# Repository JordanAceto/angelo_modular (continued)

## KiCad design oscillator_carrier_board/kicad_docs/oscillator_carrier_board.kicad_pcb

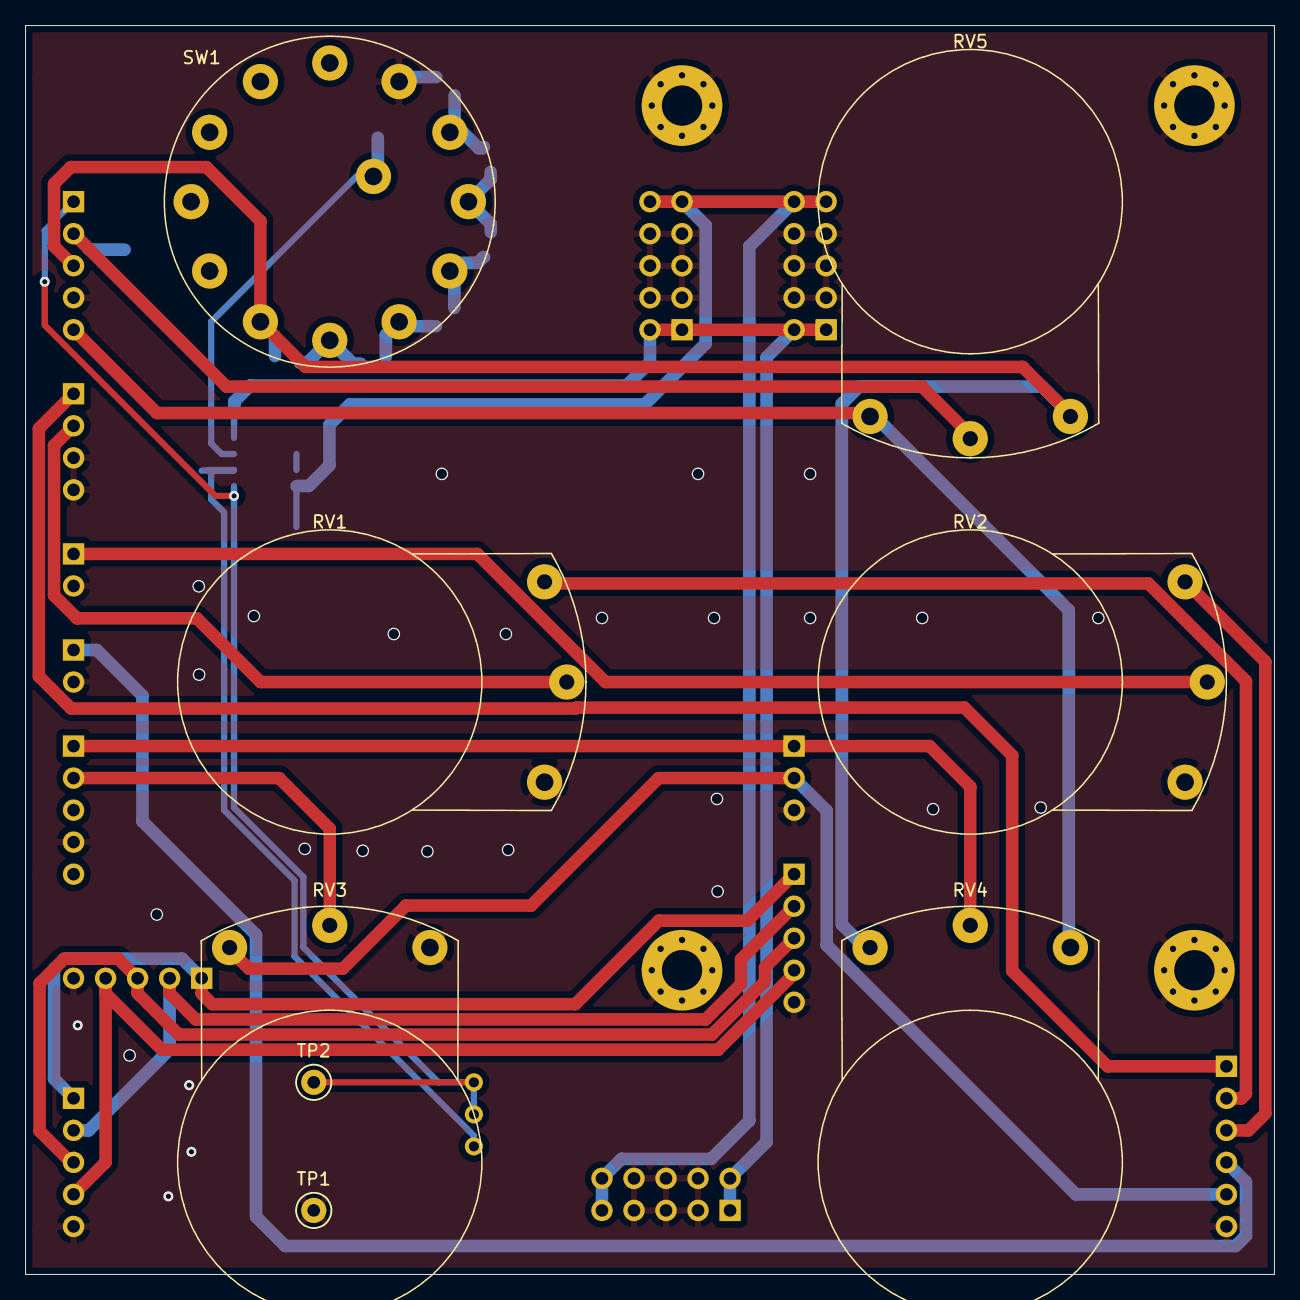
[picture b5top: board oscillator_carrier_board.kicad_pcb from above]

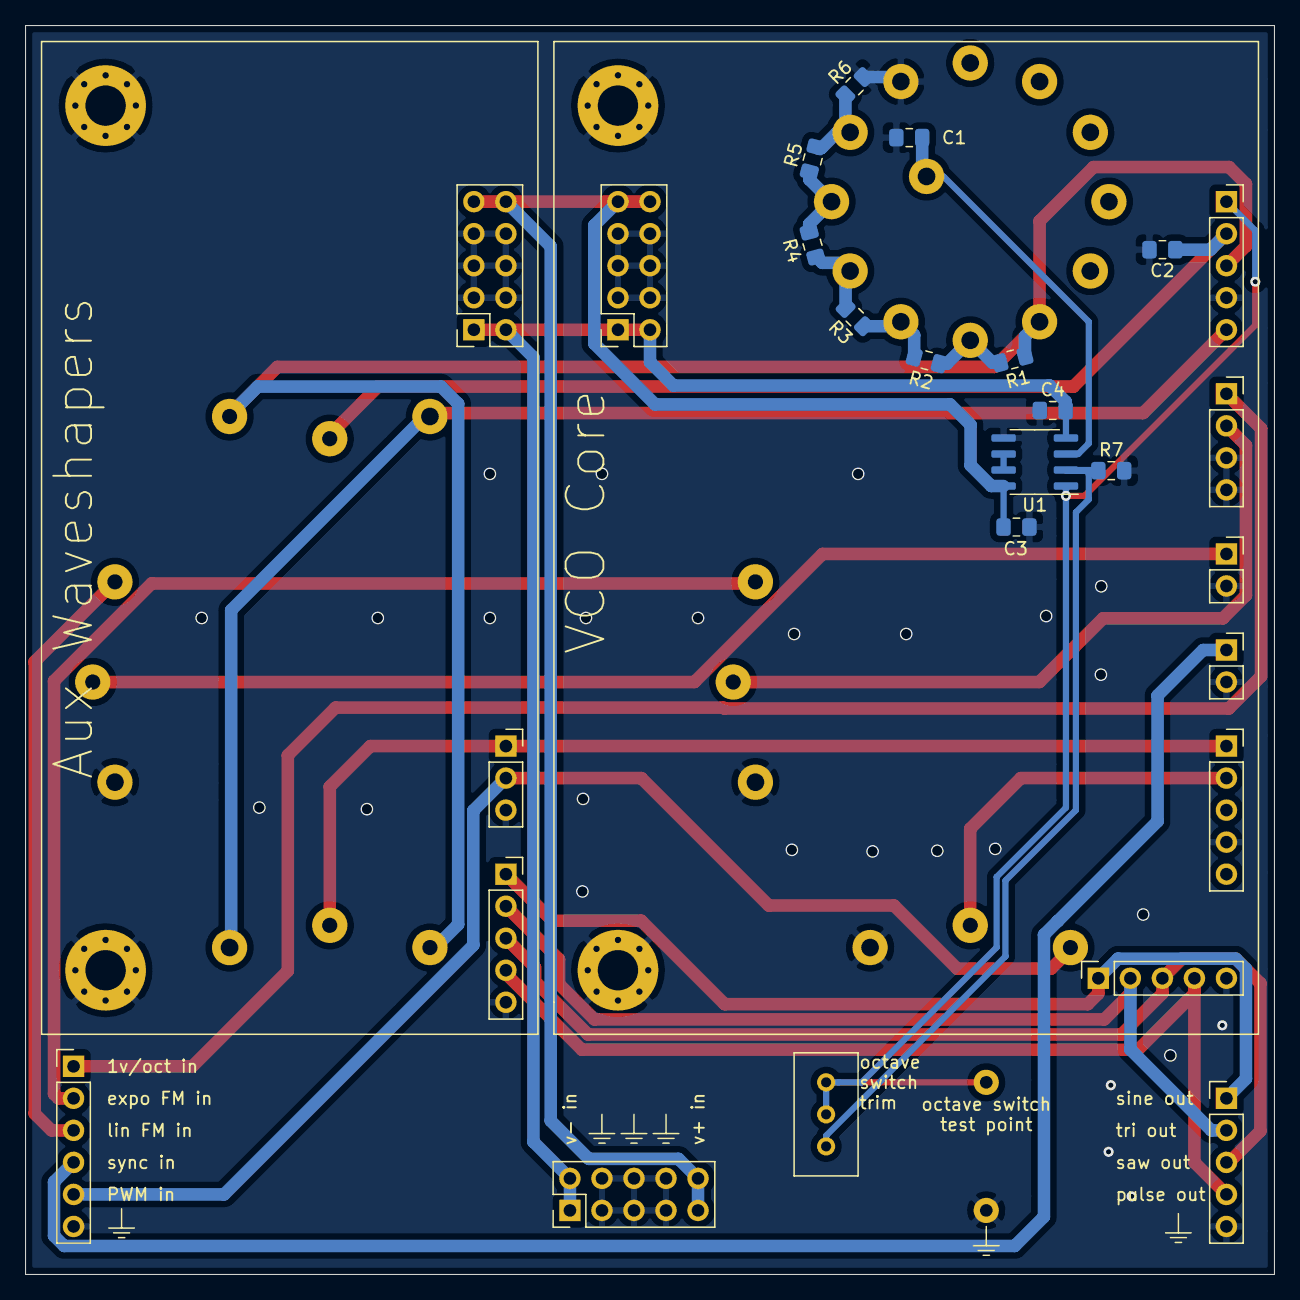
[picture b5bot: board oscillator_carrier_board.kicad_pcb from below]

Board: 2 copper layers, 99.1 x 99.1 mm, 38 parts (26 on the bottom side), 28 nets.

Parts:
C1, C2, C3, C4: 100nF; C_0805_2012Metric_Pad1.15x1.40mm_HandSolder
H1, H2, H3, H4: MountingHole_Pad; MountingHole_3.2mm_M3_Pad_Via
J1: Conn_01x06; PinHeader_1x06_P2.54mm_Vertical
J2: Conn_01x05; PinHeader_1x05_P2.54mm_Vertical
J3: power_header; PinHeader_2x05_P2.54mm_Vertical
J4: Conn_01x04; PinSocket_1x04_P2.54mm_Vertical
J5, J6: Conn_01x02; PinSocket_1x02_P2.54mm_Vertical
J7, J10, J11: Conn_01x05; PinSocket_1x05_P2.54mm_Vertical
J8, J13: power_header; PinSocket_2x05_P2.54mm_Vertical
J9: to_VCO_board; PinSocket_1x05_P2.54mm_Vertical
J12: Conn_01x03; PinSocket_1x03_P2.54mm_Vertical
R1, R2, R3, R4, R5, R6: 10k; R_0805_2012Metric_Pad1.15x1.40mm_HandSolder
R7: ???; R_0805_2012Metric_Pad1.15x1.40mm_HandSolder
RV1, RV2, RV3, RV4, RV5: 100k; alpha_RV24AF-40
RV6: ???; Potentiometer_Bourns_3296W_Vertical
SW1: octave_switch; apha_SR2612F-0112
TP1, TP2: TestPoint; TestPoint_Keystone_5000-5004_Miniature
U1: TL072; SOIC-8_3.9x4.9mm_P1.27mm

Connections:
+5V: J7.3, J10.3, R1.2, RV4.3, RV5.3, SW1.7
+12V: C3.1, J3.9, J3.10, J8.9, J8.10, J13.9, J13.10, U1.8
-5V: J7.5, J10.5, RV4.1, RV5.1
-12V: C4.2, J3.1, J3.2, J8.1, J8.2, J13.1, J13.2, U1.4
/VCO_core_components/1v_oct_in: J1.1, J4.1
/VCO_core_components/PWM_in: J1.5, J12.2, RV3.3
/VCO_core_components/expo_FM_in: J1.2, RV1.3
/VCO_core_components/lin_FM_in: J1.3, RV2.3
/VCO_core_components/sync_in: J1.4, J6.1
/aux_waveshaper_components/man_pulse_in: J7.1, J12.1, RV4.2
/aux_waveshaper_components/pulse_in: J2.4, J9.4, J11.4
/aux_waveshaper_components/saw_in: J2.3, J9.3, J11.3
/aux_waveshaper_components/sine_in: J2.1, J9.1, J11.1
/aux_waveshaper_components/tri_in: J2.2, J9.2, J11.2
GND: C1.2, C2.2, C3.2, C4.1, H1.1, H2.1, H3.1, H4.1, J1.6, J2.5, J3.3, J3.4, J3.5, J3.6, J3.7, J3.8, J4.3, J4.4, J5.2, J6.2, J7.4, J8.3, J8.4, J8.5, J8.6, J8.7, J8.8, J9.5, J10.4, J11.5, J12.3, J13.3, J13.4, J13.5, J13.6, J13.7, J13.8, R6.1, R7.2, RV1.1, RV2.1, RV3.1, SW1.1, TP1.1, U1.5
unnamed: C1.1, SW1.13, U1.3
unnamed: C2.1, J10.2, RV5.2
unnamed: J4.2, RV1.2
unnamed: J5.1, RV2.2
unnamed: J7.2, RV3.2
unnamed: J10.1, RV6.2, RV6.3, TP2.1, U1.1
unnamed: R1.1, R2.2, SW1.6
unnamed: R2.1, R3.2, SW1.5
unnamed: R3.1, R4.2, SW1.4
unnamed: R4.1, R5.2, SW1.3
unnamed: R5.1, R6.2, SW1.2
unnamed: R7.1, RV6.1, U1.2
unnamed: U1.6, U1.7

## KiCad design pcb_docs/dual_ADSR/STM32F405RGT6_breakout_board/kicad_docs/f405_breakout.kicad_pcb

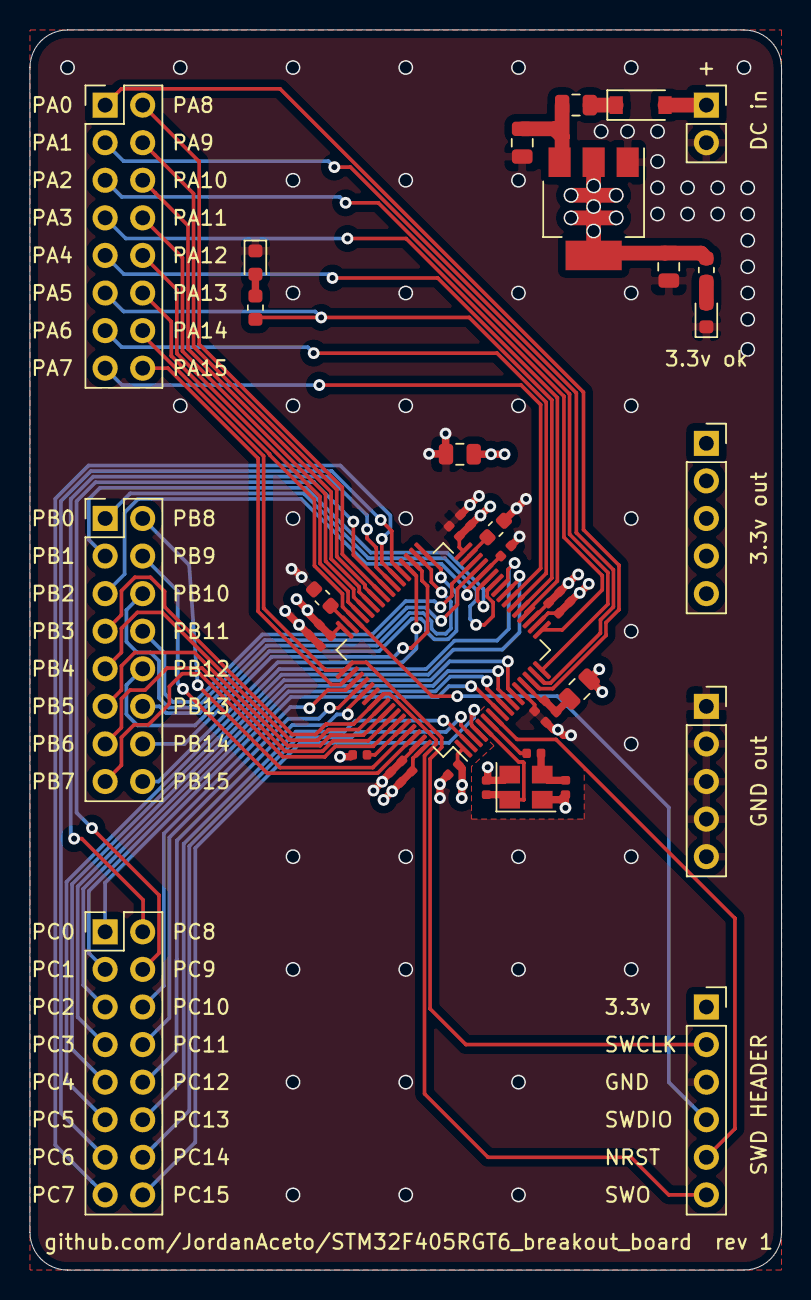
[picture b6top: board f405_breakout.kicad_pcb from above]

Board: 4 copper layers, 50.8 x 83.8 mm, 38 parts (0 on the bottom side), 63 nets.

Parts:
C1, C4, C8: 10uF; C_0805_2012Metric
C2, C3, C6, C7, C9, C10, C11, C12, C13, C14: 100nF; C_0402_1005Metric
C5: 10nF; C_0402_1005Metric
C15, C16: 2.2uF; C_0603_1608Metric
C17, C18: 12pF; C_0402_1005Metric
D1: B5819W; D_SOD-123
D2: power_LED; LED_0603_1608Metric
D3: user_LED; LED_0603_1608Metric
FB1, FB2: 100R @ 100MHz; L_0805_2012Metric
HSE1: 16MHz; Crystal_SMD_3225-4Pin_3.2x2.5mm
J1: DC_in; PinSocket_1x02_P2.54mm_Vertical
J2: SWD; PinSocket_1x06_P2.54mm_Vertical
J3: 3.3v_out; PinSocket_1x05_P2.54mm_Vertical
J4: gnd_out; PinSocket_1x05_P2.54mm_Vertical
J5: port_A; PinHeader_2x08_P2.54mm_Vertical
J6: port_B; PinHeader_2x08_P2.54mm_Vertical
J7: port_C; PinHeader_2x08_P2.54mm_Vertical
R1, R3: 2k2; R_0603_1608Metric
R2, R4: 10k; R_0402_1005Metric
R5: 100; R_0402_1005Metric
U1: AMS1117-3.3; SOT-223-3_TabPin2
U2: STM32F405RGT6; LQFP-64_10x10mm_P0.5mm

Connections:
+3.3VA: C2.1, C5.1, FB1.1, U2.13
+3V3: C1.1, C3.1, C6.1, C7.1, C8.1, C9.1, C10.1, C11.1, C12.1, C13.1, C14.1, FB1.2, J2.1, J3.1, J3.2, J3.3, J3.4, J3.5, R1.2, U1.2, U2.1, U2.19, U2.32, U2.48, U2.64
BOOT0: R2.2, U2.60
GND: C1.2, C2.2, C3.2, C4.2, C5.2, C6.2, C7.2, C8.2, C9.2, C10.2, C11.2, C12.2, C13.2, C14.2, C15.2, C16.2, C17.2, C18.2, D2.1, D3.1, HSE1.2, HSE1.4, J1.2, J2.3, J4.1, J4.2, J4.3, J4.4, J4.5, R2.1, R4.1, U1.1, U2.12, U2.18, U2.63
NRST: J2.5, U2.7
unnamed: C4.1, FB2.1, U1.3
unnamed: C15.1, U2.31
unnamed: C16.1, U2.47
unnamed: C18.1, HSE1.3, R5.2
unnamed: D1.1, FB2.2
unnamed: D2.2, R1.1
unnamed: D3.2, R3.1
PA0: J5.1, U2.14
PA1: J5.3, U2.15
PA2: J5.5, U2.16
PA3: J5.7, U2.17
PA4: J5.9, U2.20
PA5: J5.11, R3.2, U2.21
PA6: J5.13, U2.22
PA7: J5.15, U2.23
PA8: J5.2, U2.41
PA9: J5.4, U2.42
PA10: J5.6, U2.43
PA11: J5.8, U2.44
PA12: J5.10, U2.45
PA13_SWDIO: J2.4, J5.12, U2.46
PA14_SWCLK: J2.2, J5.14, U2.49
PA15: J5.16, U2.50
PB0: J6.1, U2.26
PB1: J6.3, U2.27
PB2_BOOT1: J6.5, R4.2, U2.28
PB3_SWO: J2.6, J6.7, U2.55
PB4: J6.9, U2.56
PB5: J6.11, U2.57
PB6: J6.13, U2.58
PB7: J6.15, U2.59
PB8: J6.2, U2.61
PB9: J6.4, U2.62
PB10: J6.6, U2.29
PB11: J6.8, U2.30
PB12: J6.10, U2.33
PB13: J6.12, U2.34
PB14: J6.14, U2.35
PB15: J6.16, U2.36
PC0: J7.1, U2.8
PC1: J7.3, U2.9
PC2: J7.5, U2.10
PC3: J7.7, U2.11
PC4: J7.9, U2.24
PC5: J7.11, U2.25
PC6: J7.13, U2.37
PC7: J7.15, U2.38
PC8: J7.2, U2.39
PC9: J7.4, U2.40
PC10: J7.6, U2.51
PC11: J7.8, U2.52
PC12: J7.10, U2.53
PC13: J7.12, U2.2
PC14: J7.14, U2.3
PC15: J7.16, U2.4
PH0: C17.1, HSE1.1, U2.5
PH1: R5.1, U2.6
VCC: D1.2, J1.1

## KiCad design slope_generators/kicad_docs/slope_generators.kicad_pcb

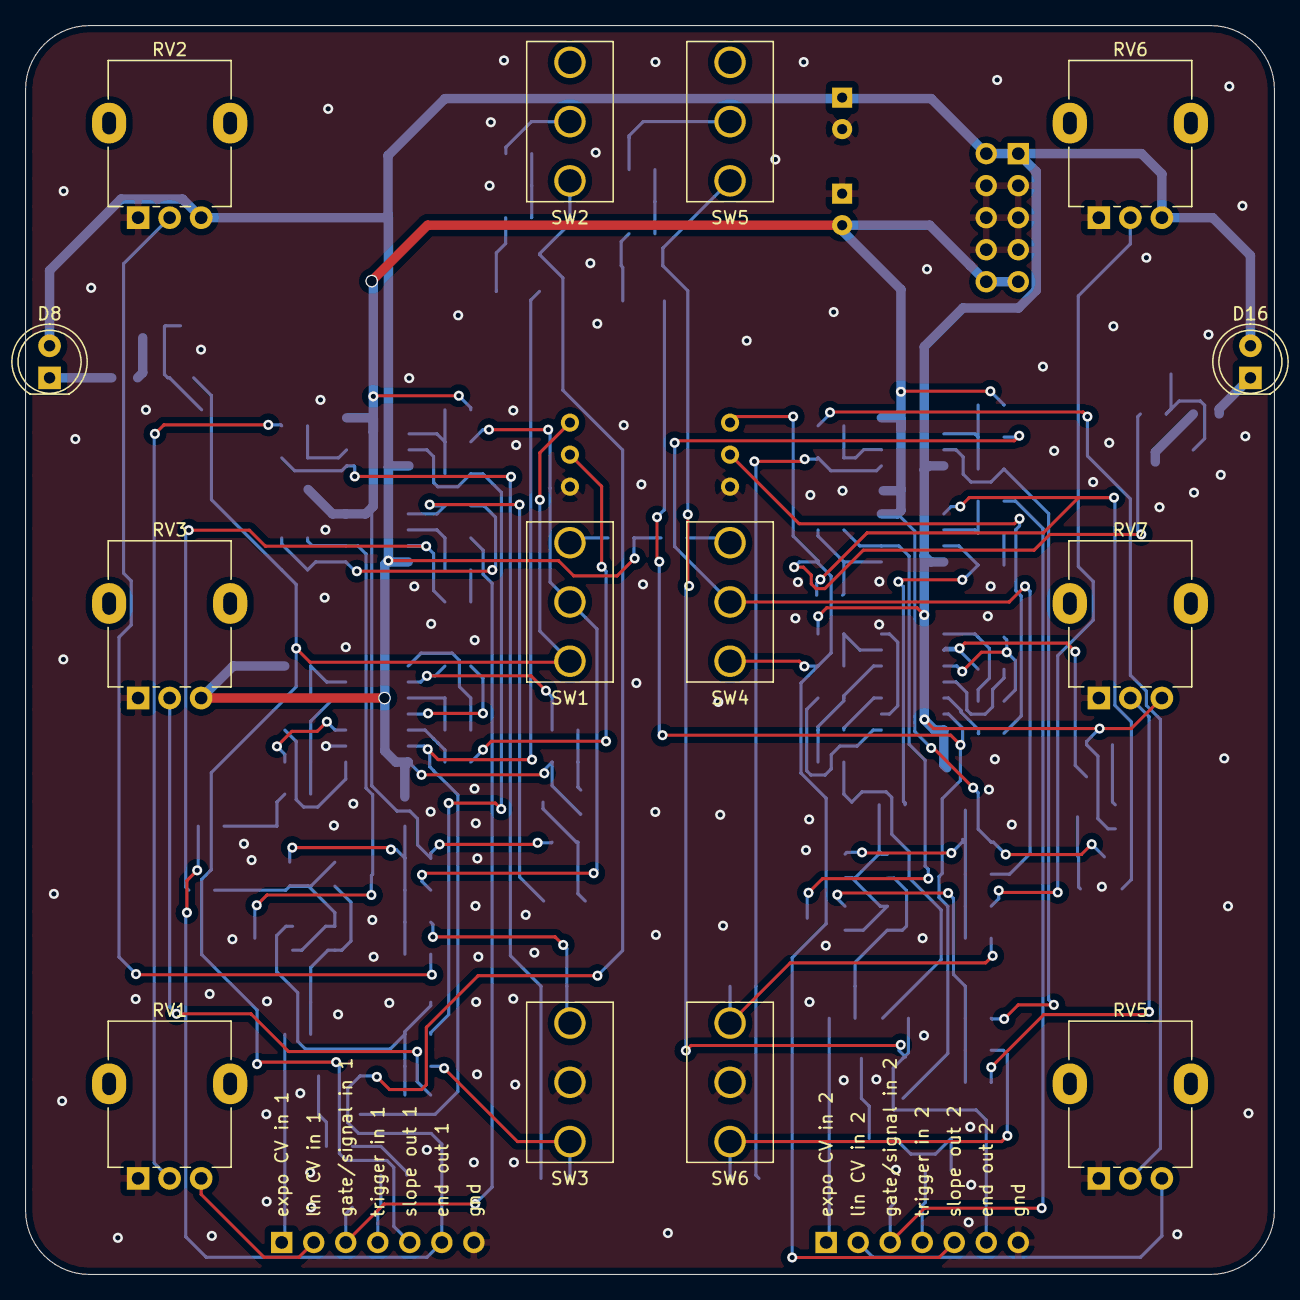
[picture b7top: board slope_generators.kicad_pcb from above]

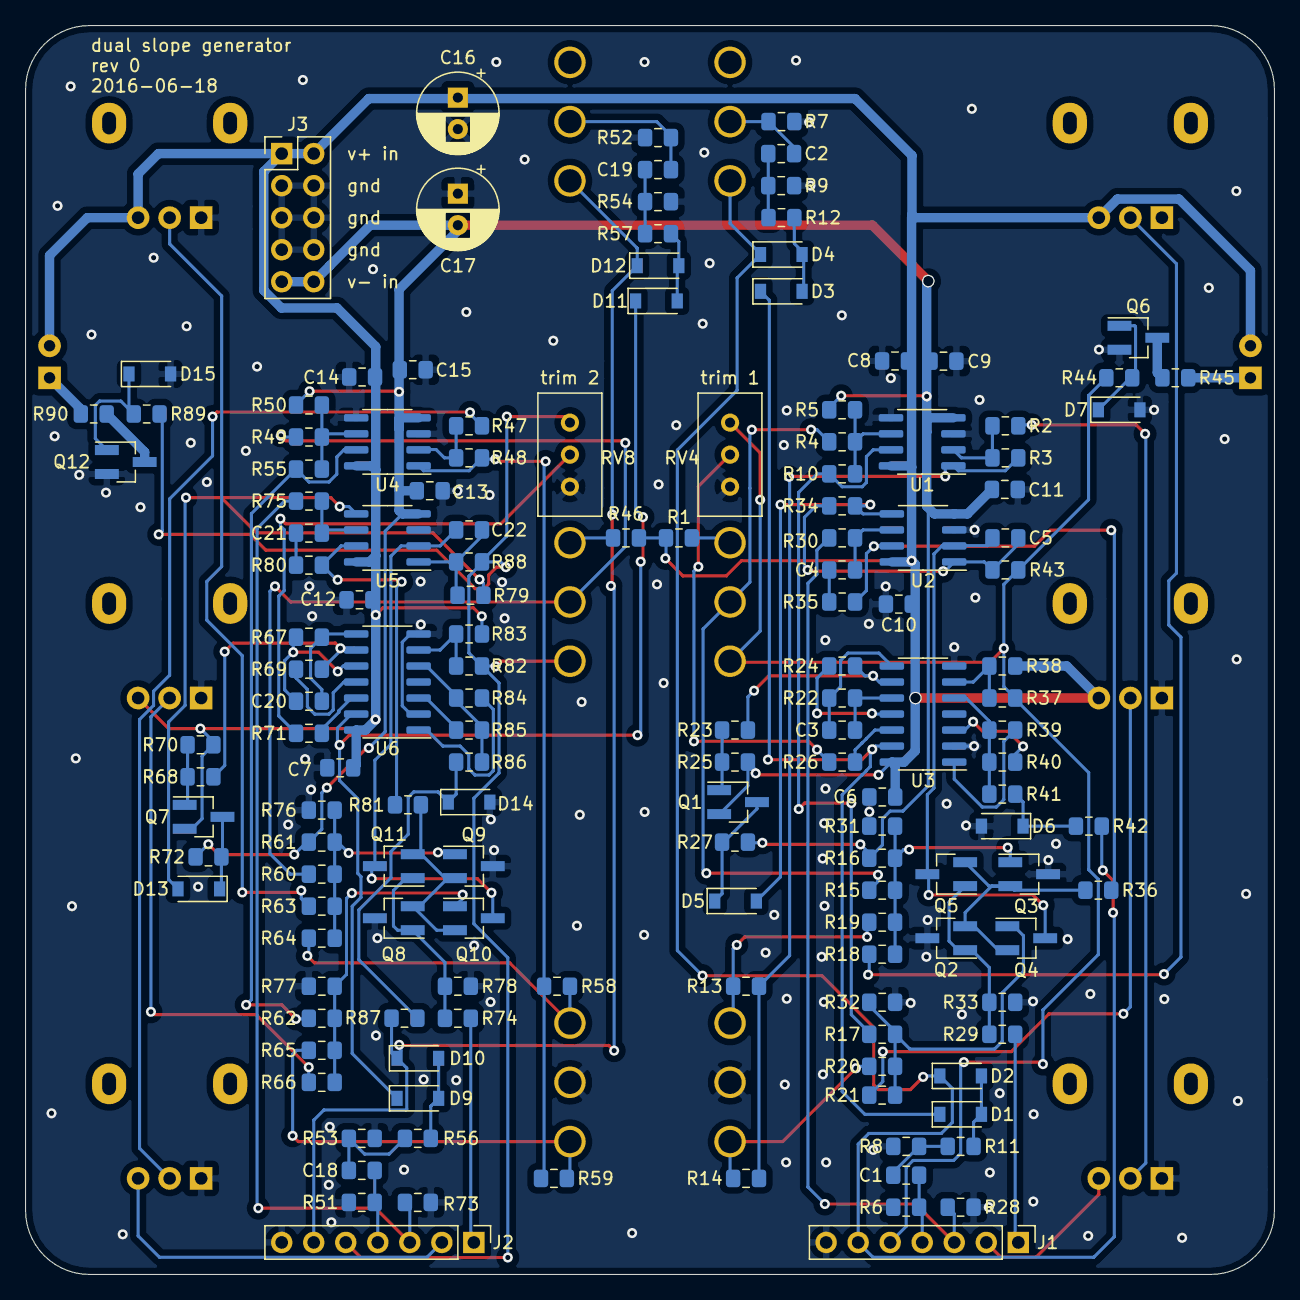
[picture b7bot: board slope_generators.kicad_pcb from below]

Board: 2 copper layers, 99.1 x 99.1 mm, 163 parts (149 on the bottom side), 101 nets.

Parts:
C1, C2, C18, C19: 1nF; C_0805_2012Metric_Pad1.15x1.40mm_HandSolder
C3, C4, C20, C21: 47pF; C_0805_2012Metric_Pad1.15x1.40mm_HandSolder
C5, C22: 22nF; C_0805_2012Metric_Pad1.15x1.40mm_HandSolder
C6, C7, C8, C9, C10, C11, C12, C13, C14, C15: 100nF; C_0805_2012Metric_Pad1.15x1.40mm_HandSolder
C16, C17: 10uF; CP_Radial_D6.3mm_P2.50mm
D1, D2, D3, D4, D5, D7, D9, D10, D11, D12, D13, D15: D; D_SOD-123
D6, D14: 5v6; D_SOD-123
D8, D16: LED; LED_D5.0mm
J1: slope_1_port; PinHeader_1x07_P2.54mm_Vertical
J2: slope_2_port; PinHeader_1x07_P2.54mm_Vertical
J3: power_in; PinHeader_2x05_P2.54mm_Vertical
Q1, Q2, Q4, Q7, Q8, Q10: MMBT3906; SOT-23_Handsoldering
Q3, Q5, Q6, Q9, Q11, Q12: MMBT3904; SOT-23_Handsoldering
R1, R46: 270k; R_0805_2012Metric_Pad1.15x1.40mm_HandSolder
R2, R3, R4, R6, R7, R8, R9, R10, R15, R17, R28, R30, R47, R48, R49, R51, R52, R53, R54, R55, R60, R62, R73, R75: 100k; R_0805_2012Metric_Pad1.15x1.40mm_HandSolder
R5, R16, R50, R61: 560k; R_0805_2012Metric_Pad1.15x1.40mm_HandSolder
R11, R12, R13, R14, R56, R57, R58, R59: 33k; R_0805_2012Metric_Pad1.15x1.40mm_HandSolder
R18, R21, R29, R63, R66, R74: 82k; R_0805_2012Metric_Pad1.15x1.40mm_HandSolder
R19, R20, R64, R65: 47k; R_0805_2012Metric_Pad1.15x1.40mm_HandSolder
R22, R24, R67, R69: 820k; R_0805_2012Metric_Pad1.15x1.40mm_HandSolder
R23, R26, R27, R34, R68, R71, R72, R79: 220k; R_0805_2012Metric_Pad1.15x1.40mm_HandSolder
R25, R70: 68k; R_0805_2012Metric_Pad1.15x1.40mm_HandSolder
R31, R32, R41, R76, R77, R86: 2k2; R_0805_2012Metric_Pad1.15x1.40mm_HandSolder
R33, R78: 1k8; R_0805_2012Metric_Pad1.15x1.40mm_HandSolder
R35, R38, R80, R83: 10M; R_0805_2012Metric_Pad1.15x1.40mm_HandSolder
R36, R81: 8k2; R_0805_2012Metric_Pad1.15x1.40mm_HandSolder
R37, R82: 330k; R_0805_2012Metric_Pad1.15x1.40mm_HandSolder
R39, R40, R84, R85: 1M; R_0805_2012Metric_Pad1.15x1.40mm_HandSolder
R42, R45, R87, R90: 1k; R_0805_2012Metric_Pad1.15x1.40mm_HandSolder
R43, R88: 100; R_0805_2012Metric_Pad1.15x1.40mm_HandSolder
R44, R89: 150k; R_0805_2012Metric_Pad1.15x1.40mm_HandSolder
RV1, RV2, RV3, RV5, RV6, RV7: 100k; Potentiometer_Alpha_RD901F-40-00D_Single_Vertical
RV4, RV8: 100k; Potentiometer_Bourns_3296W_Vertical
SW1, SW4: lin_expo_switch; SPDT_on_on
SW2, SW5: auto_cycle_switch; SPDT_on_on
SW3, SW6: rise-fall-both-switch; SPDT_on_on
U1, U2, U4, U5: TL072; SOIC-8_3.9x4.9mm_P1.27mm
U3, U6: LM3900; SOIC-14_3.9x8.7mm_P1.27mm

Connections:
+12V: C6.1, C7.1, C8.1, C10.1, C12.1, C14.1, C16.1, D8.2, D16.2, J3.1, J3.2, Q1.2, Q7.2, R1.1, R25.2, R38.2, R46.1, R70.2, R83.2, RV2.3, RV3.3, RV6.3, RV7.3, U1.8, U2.8, U3.14, U4.8, U5.8, U6.14
-12V: C9.2, C11.2, C13.2, C15.2, C17.2, J3.9, J3.10, R5.1, R16.1, R27.1, R50.1, R61.1, R72.1, U1.4, U2.4, U4.4, U5.4
/slope_1_end_out: D2.1, D4.1, J1.6, R42.1, SW2.3
/slope_1_out: J1.5, R37.2, R43.1, R44.2, RV4.3, SW1.3
/slope_2_end_out: D10.1, D12.1, J2.6, R87.1, SW5.3
/slope_2_out: J2.5, R82.2, R88.1, R89.2, RV8.3, SW4.3
/slope_generator_1/CV_in: J1.2, RV1.3
/slope_generator_1/expo_CV_in: J1.1, R29.2
/slope_generator_1/fall_CV: Q4.1, R17.2, R20.1, R21.1, R32.1
/slope_generator_1/gate_in: J1.3, R28.2, R30.2
/slope_generator_1/rise_CV: Q3.1, R15.2, R16.2, R18.1, R19.1, R31.1
/slope_generator_1/trig_in: C1.2, J1.4, R6.1
/slope_generator_2/CV_in: J2.2, RV5.3
/slope_generator_2/expo_CV_in: J2.1, R74.2
/slope_generator_2/fall_CV: Q10.1, R62.2, R65.1, R66.1, R77.1
/slope_generator_2/gate_in: J2.3, R73.2, R75.2
/slope_generator_2/rise_CV: Q9.1, R60.2, R61.2, R63.1, R64.1, R76.1
/slope_generator_2/trig_in: C18.2, J2.4, R51.1
GND: C6.2, C7.2, C8.2, C9.1, C10.2, C11.1, C12.2, C13.1, C14.2, C15.1, C16.2, C17.1, D6.2, D7.2, D14.2, D15.2, J1.7, J2.7, J3.3, J3.4, J3.5, J3.6, J3.7, J3.8, Q2.3, Q3.3, Q6.2, Q8.3, Q9.3, Q12.2, R6.2, R7.2, R8.2, R9.2, R28.1, R31.2, R32.2, R33.2, R51.2, R52.2, R53.2, R54.2, R73.1, R76.2, R77.2, R78.2, RV1.1, RV2.1, RV3.1, RV4.1, RV5.1, RV6.1, RV7.1, RV8.1, SW3.2, SW6.2, U1.3, U1.5, U2.3, U3.2, U3.7, U4.3, U4.5, U5.3, U6.2, U6.7
unnamed: C1.1, R8.1, R11.2
unnamed: C2.1, R9.1, R12.2
unnamed: C2.2, R7.1, SW2.2
unnamed: C3.1, R22.1, U3.10
unnamed: C3.2, R22.2, U3.8
unnamed: C4.1, R35.2
unnamed: C4.2, R30.1, U2.6
unnamed: C5.1, R34.1, R43.2, U2.1
unnamed: C5.2, Q4.3, Q5.3, U2.2
unnamed: C18.1, R53.1, R56.2
unnamed: C19.1, R54.1, R57.2
unnamed: C19.2, R52.1, SW5.2
unnamed: C20.1, R67.1, U6.10
unnamed: C20.2, R67.2, U6.8
unnamed: C21.1, R80.2
unnamed: C21.2, R75.1, U5.6
unnamed: C22.1, R79.1, R88.2, U5.1
unnamed: C22.2, Q10.3, Q11.3, U5.2
unnamed: D1.1, D3.1, U3.13
unnamed: D1.2, D2.2, R11.1
unnamed: D3.2, D4.2, R12.1
unnamed: D5.1, Q1.3, R27.2
unnamed: D5.2, R34.2, U2.5
unnamed: D6.1, R41.1, R42.2
unnamed: D7.1, Q6.1, R44.1
unnamed: D8.1, R45.2
unnamed: D9.2, D10.2, R56.1
unnamed: D9.1, D11.1, U6.13
unnamed: D11.2, D12.2, R57.1
unnamed: D13.1, Q7.3, R72.2
unnamed: D13.2, R79.2, U5.5
unnamed: D14.1, R86.1, R87.2
unnamed: D15.1, Q12.1, R89.1
unnamed: D16.1, R90.2
unnamed: Q1.1, R23.2, R25.1
unnamed: Q2.1, Q5.1, R29.1, R33.1
unnamed: Q2.2, Q3.2, Q4.2, Q5.2, R36.1
unnamed: Q6.3, R45.1
unnamed: Q7.1, R68.2, R70.1
unnamed: Q8.2, Q9.2, Q10.2, Q11.2, R81.1
unnamed: Q8.1, Q11.1, R74.1, R78.1
unnamed: Q12.3, R90.1
unnamed: R1.2, SW1.1
unnamed: R2.1, R3.2, U1.2
unnamed: R2.2, RV1.2
unnamed: R4.2, R5.2, R10.1, U1.6
unnamed: R10.2, R17.1, U1.7
unnamed: R13.1, R19.2, SW3.1
unnamed: R3.1, R13.2, R14.2, U1.1
unnamed: R14.1, R20.2, SW3.3
unnamed: R4.1, R15.1, SW1.2
unnamed: R18.2, RV2.2
unnamed: R21.2, RV3.2
unnamed: R23.1, R24.2, U3.9
unnamed: R24.1, U3.11
unnamed: R26.1, U3.12
unnamed: R26.2, RV4.2
unnamed: R35.1, R36.2, U2.7
unnamed: R37.1, R38.1, U3.6
unnamed: R39.1, R40.1, R41.2, U3.5
unnamed: R39.2, U3.1
unnamed: R40.2, U3.3
unnamed: R46.2, SW4.1
unnamed: R47.1, R48.2, U4.2
unnamed: R47.2, RV5.2
unnamed: R48.1, R58.2, R59.2, U4.1
unnamed: R49.1, R60.1, SW4.2
unnamed: R49.2, R50.2, R55.1, U4.6
unnamed: R55.2, R62.1, U4.7
unnamed: R58.1, R64.2, SW6.1
unnamed: R59.1, R65.2, SW6.3
unnamed: R63.2, RV6.2
unnamed: R66.2, RV7.2
unnamed: R68.1, R69.2, U6.9
unnamed: R69.1, U6.11
unnamed: R71.1, U6.12
unnamed: R71.2, RV8.2
unnamed: R80.1, R81.2, U5.7
unnamed: R82.1, R83.1, U6.6
unnamed: R84.1, R85.1, R86.2, U6.5
unnamed: R84.2, U6.1
unnamed: R85.2, U6.3
